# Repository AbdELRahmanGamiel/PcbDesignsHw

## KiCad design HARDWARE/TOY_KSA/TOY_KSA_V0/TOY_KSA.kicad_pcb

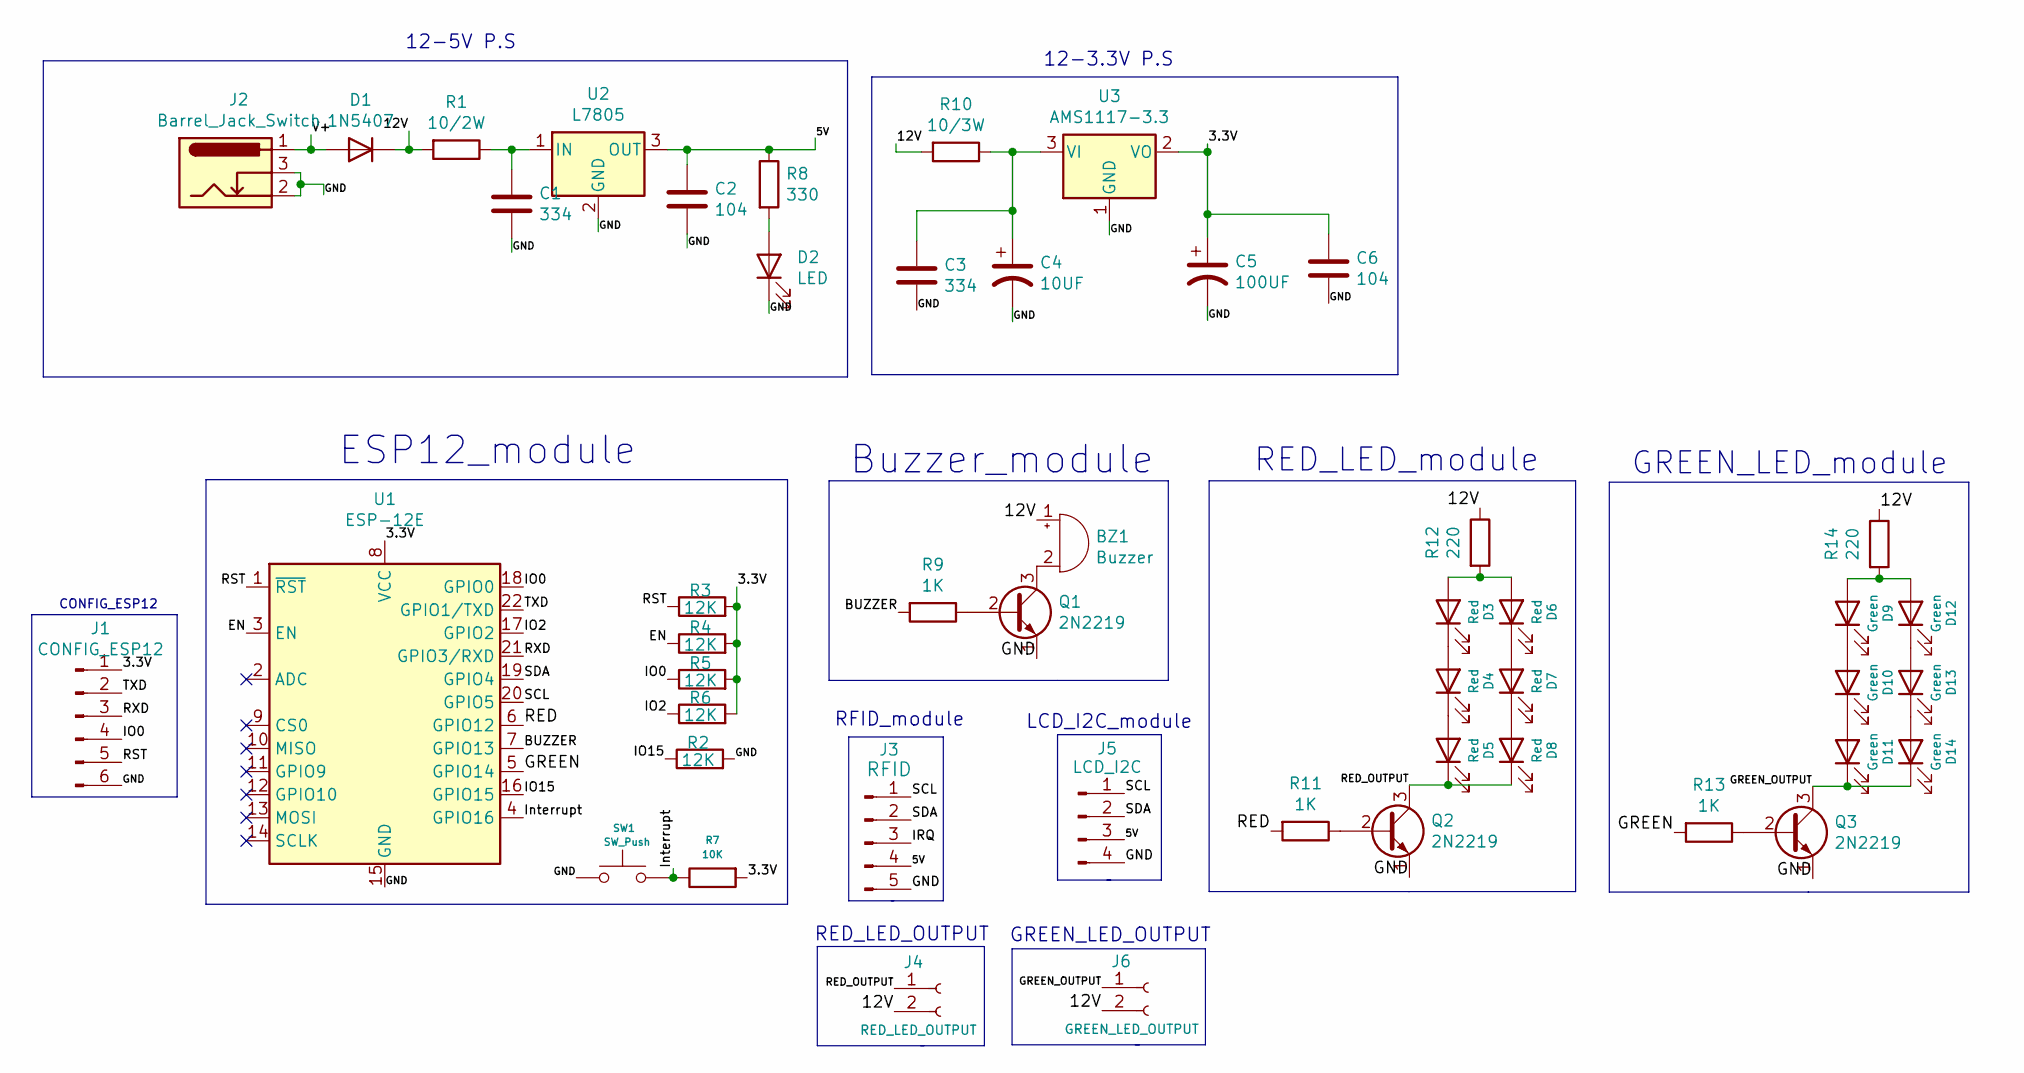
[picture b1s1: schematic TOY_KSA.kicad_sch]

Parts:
BZ1: Buzzer; Buzzer_12x9.5RM7.6
C1, C3: 334; C_0805_2012Metric_Pad1.18x1.45mm_HandSolder
C2, C6: 104; C_0805_2012Metric_Pad1.18x1.45mm_HandSolder
C4: 10UF; CP_Radial_D5.0mm_P2.00mm
C5: 100UF; CP_Radial_D8.0mm_P3.50mm
D1: 1N5407; D_SMA_Handsoldering
D2: LED; LED_0805_2012Metric_Pad1.15x1.40mm_HandSolder
D3, D4, D5, D6, D7, D8: Red; LED_0805_2012Metric_Pad1.15x1.40mm_HandSolder
D9, D10, D11, D12, D13, D14: Green; LED_0805_2012Metric_Pad1.15x1.40mm_HandSolder
J1: CONFIG_ESP12; PinHeader_1x06_P2.54mm_Vertical
J2: Barrel_Jack_Switch; BarrelJack_Horizontal
J3: RFID; PinHeader_1x05_P2.54mm_Vertical
J4: RED_LED_OUTPUT; PinHeader_1x02_P2.54mm_Vertical
J5: LCD_I2C; PinHeader_1x04_P2.54mm_Vertical
J6: GREEN_LED_OUTPUT; PinHeader_1x02_P2.54mm_Vertical
Q1, Q2, Q3: 2N2219; TO-92L_Wide
R1: 10/2W; R_Axial_Power_L20.0mm_W6.4mm_P25.40mm
R2, R3, R4, R5, R6: 12K; R_0805_2012Metric_Pad1.20x1.40mm_HandSolder
R7: 10K; R_0805_2012Metric_Pad1.20x1.40mm_HandSolder
R8: 330; R_0805_2012Metric_Pad1.20x1.40mm_HandSolder
R9, R11, R13: 1K; R_0805_2012Metric_Pad1.20x1.40mm_HandSolder
R10: 10/3W; R_Axial_Power_L20.0mm_W6.4mm_P25.40mm
R12, R14: 220; R_0805_2012Metric_Pad1.20x1.40mm_HandSolder
SW1: SW_Push; SW_PUSH_6mm_H7.3mm
U1: ESP-12E
U2: L7805; SOT-223-3_TabPin2
U3: AMS1117-3.3; SOT-223-3_TabPin2

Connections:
/3.3V: C5.1, C6.1, J1.1, R3.2, R4.2, R5.2, R6.2, R7.2, U1.8 (VCC), U3.2 (VO)
/5V: C2.1, J3.4, J5.3, R8.1, U2.3 (OUT)
/12V: BZ1.1 (-), D1.1 (K), J4.2, J6.2, R1.2, R10.2, R12.1, R14.1
/BUZZER: R9.2, U1.7 (GPIO13)
/EN: R4.1, U1.3 (EN)
/GND: C1.2, C2.2, C3.2, C4.2, C5.2, C6.2, D2.1 (K), J1.6, J2.2, J2.3, J3.5, J5.4, Q1.1 (E), Q2.1 (E), Q3.1 (E), R2.2, SW1.1, U1.15 (GND), U2.2 (GND), U3.1 (GND)
/GREEN: R13.2, U1.5 (GPIO14)
/GREEN_OUTPUT: D11.1 (K), D14.1 (K), J6.1, Q3.3 (C)
/IO0: J1.4, R5.1, U1.18 (GPIO0)
/IO2: R6.1, U1.17 (GPIO2)
/IO15: R2.1, U1.16 (GPIO15)
/IRQ: J3.3
/Interrupt: R7.1, SW1.2, U1.4 (GPIO16)
/RED: R11.2, U1.6 (GPIO12)
/RED_OUTPUT: D5.1 (K), D8.1 (K), J4.1, Q2.3 (C)
/RST: J1.5, R3.1, U1.1 (~RST)
/RXD: J1.3, U1.21 (GPIO3/RXD)
/SCL: J3.1, J5.1, U1.20 (GPIO5)
/SDA: J3.2, J5.2, U1.19 (GPIO4)
/TXD: J1.2, U1.22 (GPIO1/TXD)
/V+: D1.2 (A), J2.1
unnamed: BZ1.2 (+), Q1.3 (C)
unnamed: C1.1, R1.1, U2.1 (IN)
unnamed: C3.1, C4.1, R10.1, U3.3 (VI)
unnamed: D2.2 (A), R8.2
unnamed: D3.1 (K), D4.2 (A)
unnamed: D3.2 (A), D6.2 (A), R12.2
unnamed: D4.1 (K), D5.2 (A)
unnamed: D6.1 (K), D7.2 (A)
unnamed: D7.1 (K), D8.2 (A)
unnamed: D10.1 (K), D11.2 (A)
unnamed: D9.1 (K), D10.2 (A)
unnamed: D12.1 (K), D13.2 (A)
unnamed: D9.2 (A), D12.2 (A), R14.2
unnamed: D13.1 (K), D14.2 (A)
unnamed: Q1.2 (B), R9.1
unnamed: Q2.2 (B), R11.1
unnamed: Q3.2 (B), R13.1

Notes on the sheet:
GREEN_LED_module
ESP12_module
GREEN_LED_OUTPUT
RED_LED_module
Buzzer_module
12-3.3V P.S
CONFIG_ESP12
12-5V P.S
RFID_module
LCD_I2C_module
RED_LED_OUTPUT

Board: 2 copper layers, 48 parts (0 on the bottom side), 37 nets, no tracks yet.

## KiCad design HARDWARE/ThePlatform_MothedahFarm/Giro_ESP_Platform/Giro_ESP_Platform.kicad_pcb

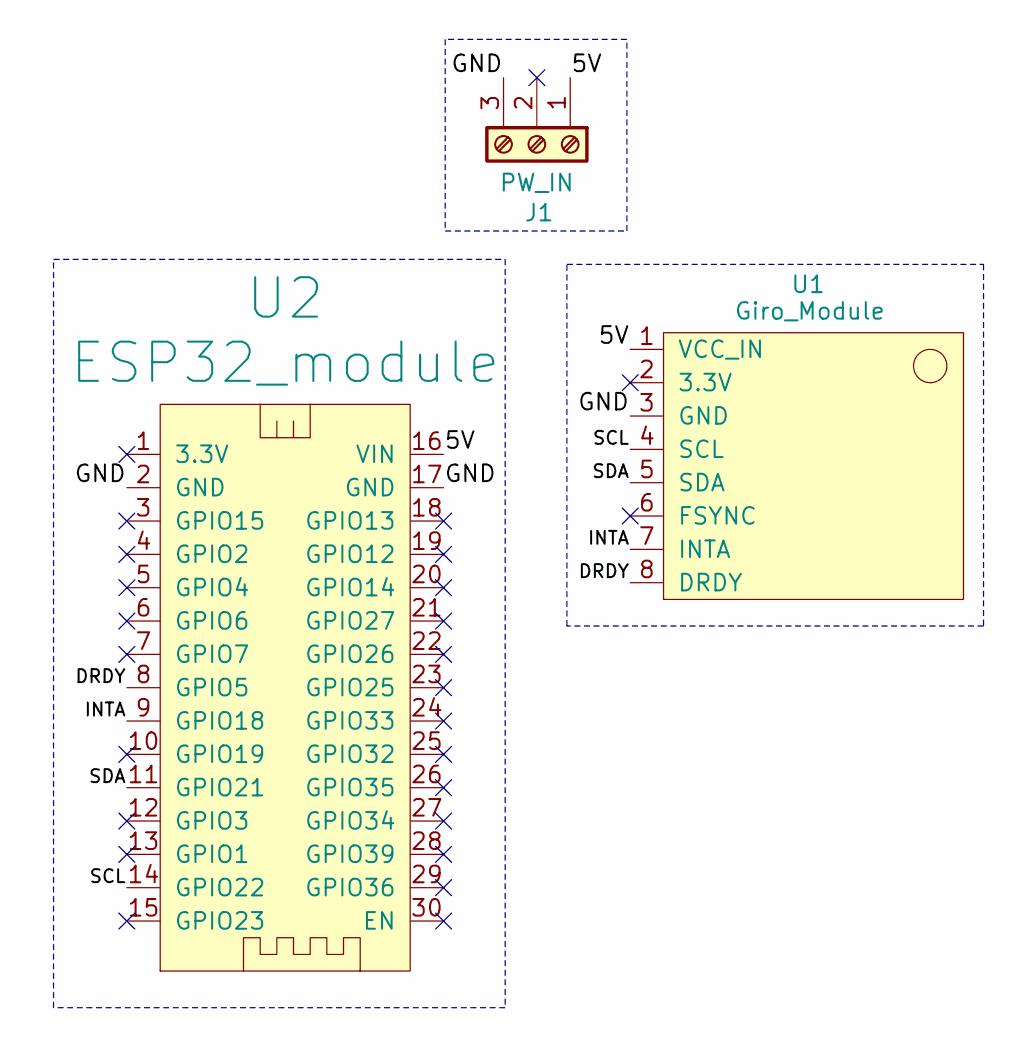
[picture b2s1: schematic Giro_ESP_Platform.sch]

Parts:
J1: PW_IN; PhoenixContact_MSTBA_2,5_3-G-5,08_1x03_P5.08mm_Horizontal
U1: Giro_Module
U2: ESP32_module

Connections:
/5V: J1.1, U1.1 (VCC_IN), U2.16 (VIN)
/DRDY: U1.8 (DRDY), U2.8 (GPIO5)
/GND: J1.3, U1.3 (GND), U2.2 (GND), U2.17 (GND)
/INTA: U1.7 (INTA), U2.9 (GPIO18)
/SCL: U1.4 (SCL), U2.14 (GPIO22)
/SDA: U1.5 (SDA), U2.11 (GPIO21)

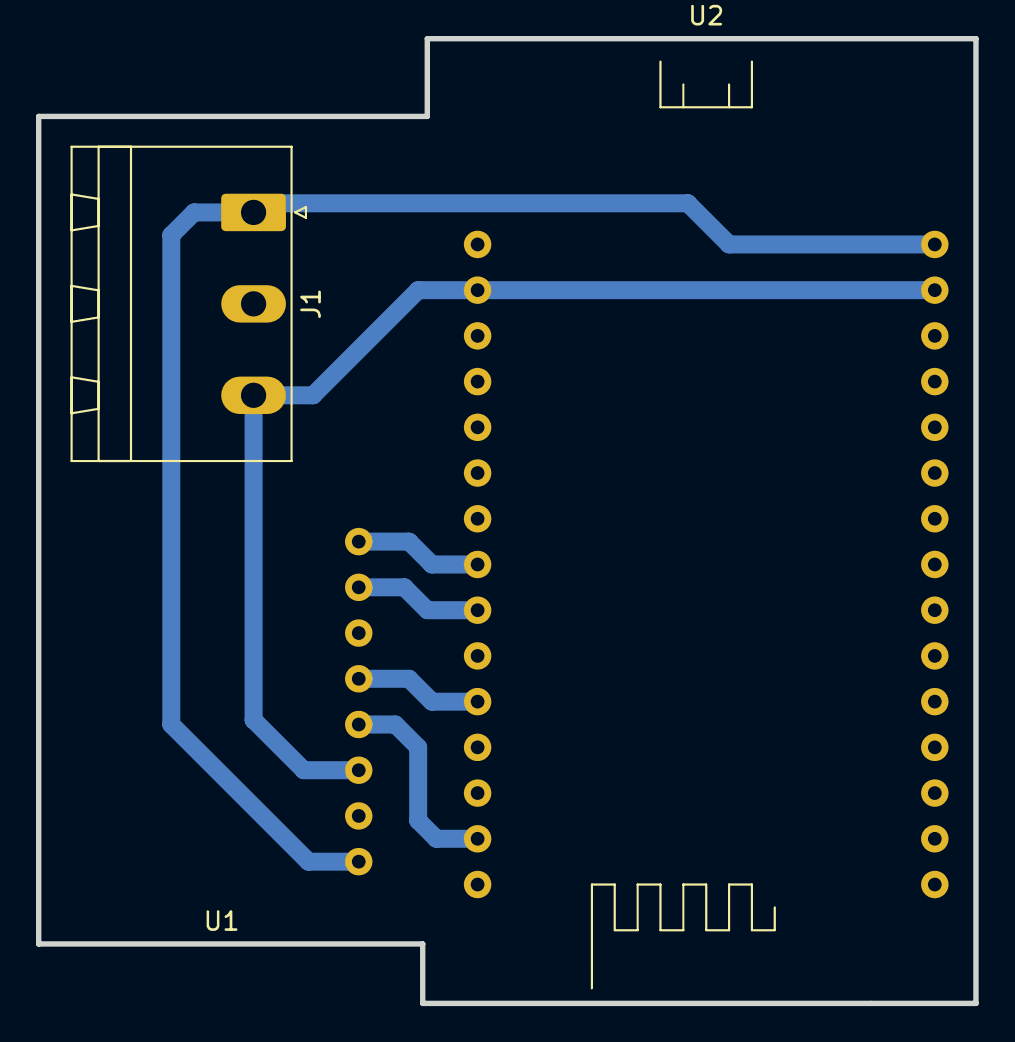
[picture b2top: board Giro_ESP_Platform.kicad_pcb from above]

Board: 2 copper layers, 52.1 x 53.6 mm, 3 parts (0 on the bottom side), 6 nets.

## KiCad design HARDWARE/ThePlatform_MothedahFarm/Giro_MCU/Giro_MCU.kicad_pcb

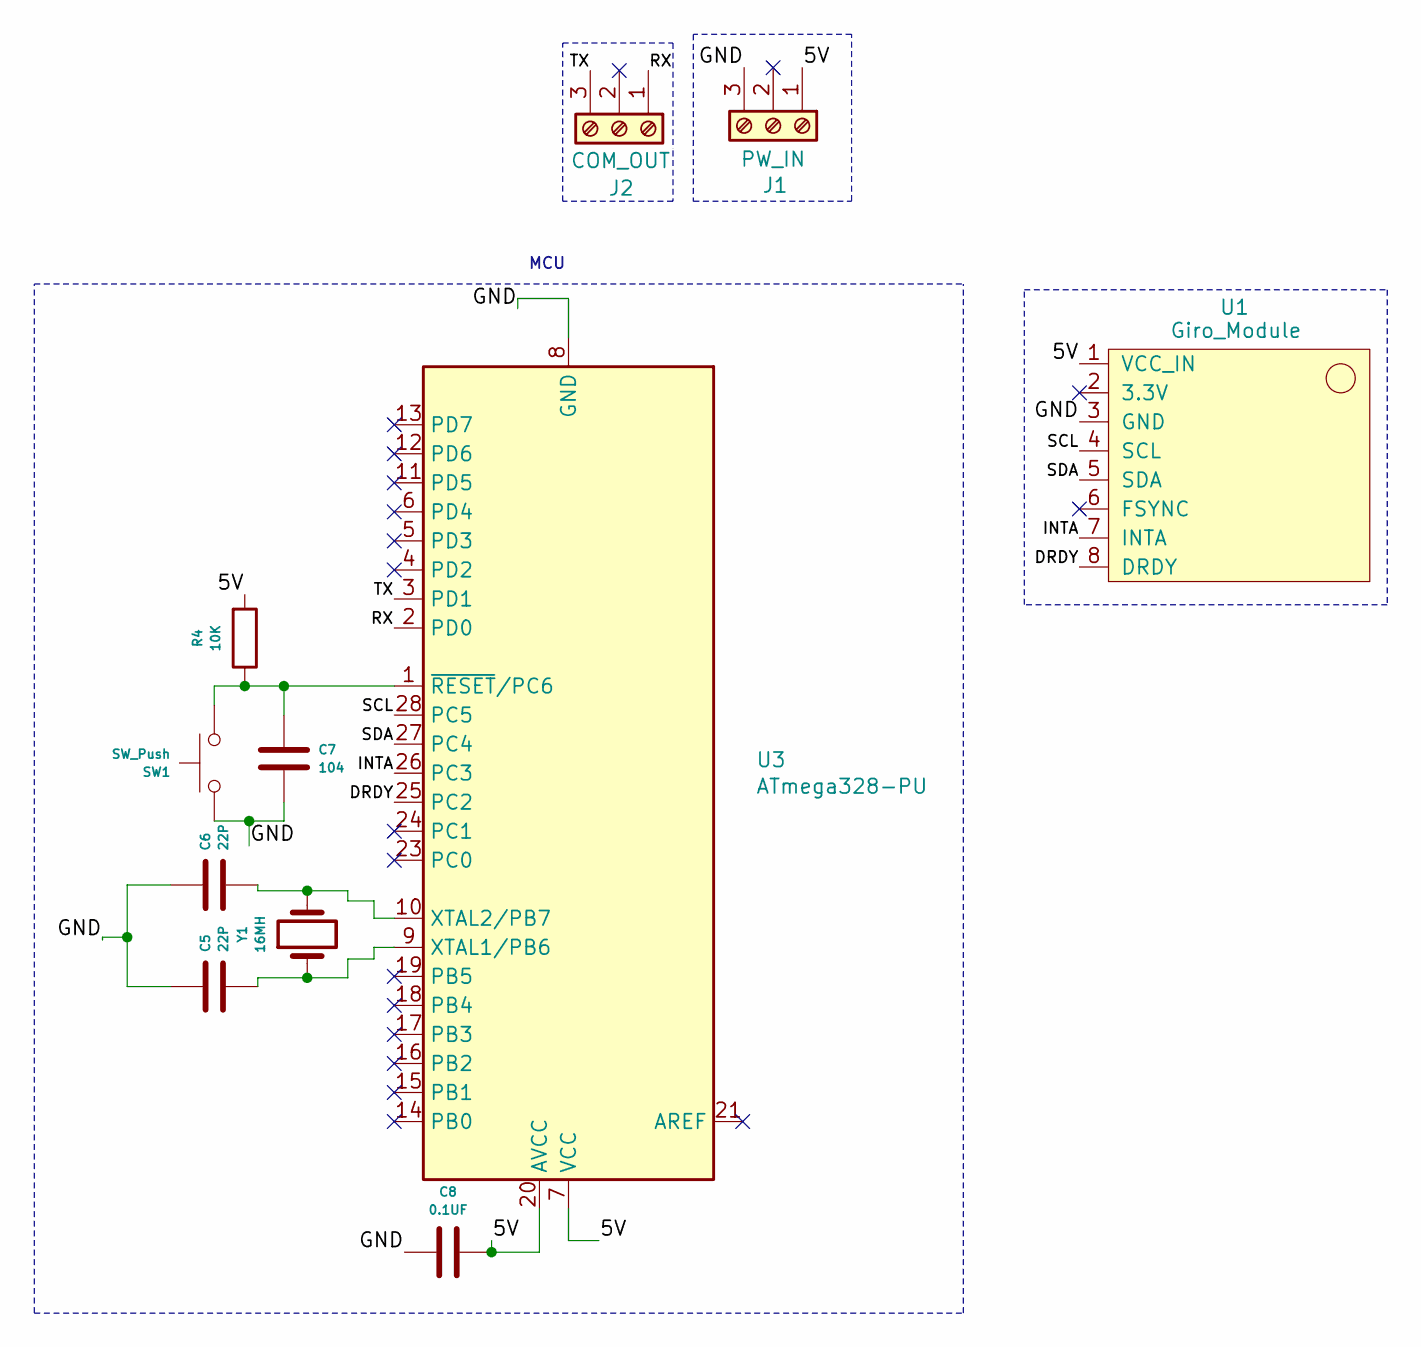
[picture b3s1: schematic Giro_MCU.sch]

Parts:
C5, C6: 22P; C_Disc_D7.0mm_W2.5mm_P5.00mm
C7: 104; C_Disc_D7.0mm_W2.5mm_P5.00mm
C8: 0.1UF; C_Disc_D7.0mm_W2.5mm_P5.00mm
J1: PW_IN; PhoenixContact_MSTBA_2,5_3-G-5,08_1x03_P5.08mm_Horizontal
J2: COM_OUT; PhoenixContact_MSTBA_2,5_3-G-5,08_1x03_P5.08mm_Horizontal
R4: 10K; R_Axial_DIN0207_L6.3mm_D2.5mm_P10.16mm_Horizontal
SW1: SW_Push; SW_PUSH_6mm_H7.3mm
U1: Giro_Module
U3: ATmega328-PU; DIP-28_W7.62mm_Socket_LongPads
Y1: 16MH; Resonator-2Pin_W10.0mm_H5.0mm

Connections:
/5V: C8.1, J1.1, R4.2, U1.1 (VCC_IN), U3.7 (VCC), U3.20 (AVCC)
/DRDY: U1.8 (DRDY), U3.25 (PC2)
/GND: C5.2, C6.2, C7.1, C8.2, J1.3, SW1.1, U1.3 (GND), U3.8 (GND), U3.22 (GND)
/INTA: U1.7 (INTA), U3.26 (PC3)
/RX: J2.1, U3.2 (PD0)
/SCL: U1.4 (SCL), U3.28 (PC5)
/SDA: U1.5 (SDA), U3.27 (PC4)
/TX: J2.3, U3.3 (PD1)
unnamed: C5.1, U3.9 (XTAL1/PB6), Y1.1
unnamed: C6.1, U3.10 (XTAL2/PB7), Y1.2
unnamed: C7.2, R4.1, SW1.2, U3.1 (~RESET~/PC6)

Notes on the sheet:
MCU

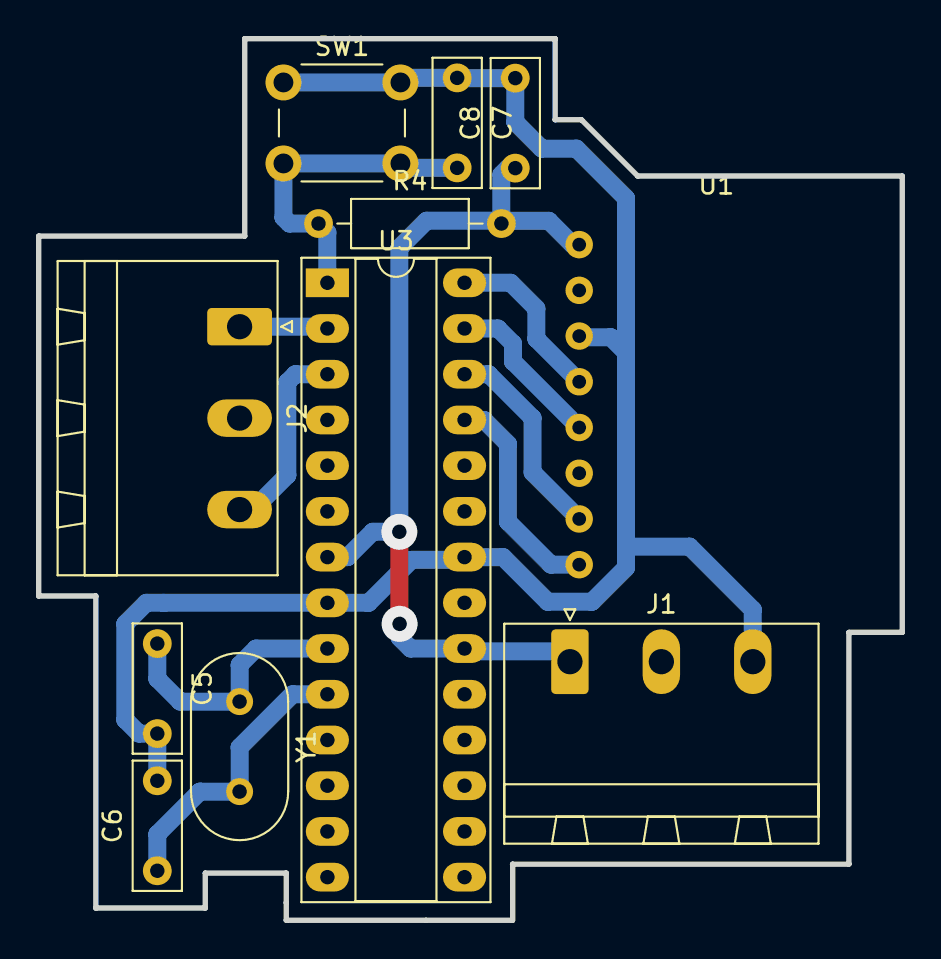
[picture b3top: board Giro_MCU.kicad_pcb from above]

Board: 2 copper layers, 48.0 x 49.0 mm, 11 parts (0 on the bottom side), 11 nets.

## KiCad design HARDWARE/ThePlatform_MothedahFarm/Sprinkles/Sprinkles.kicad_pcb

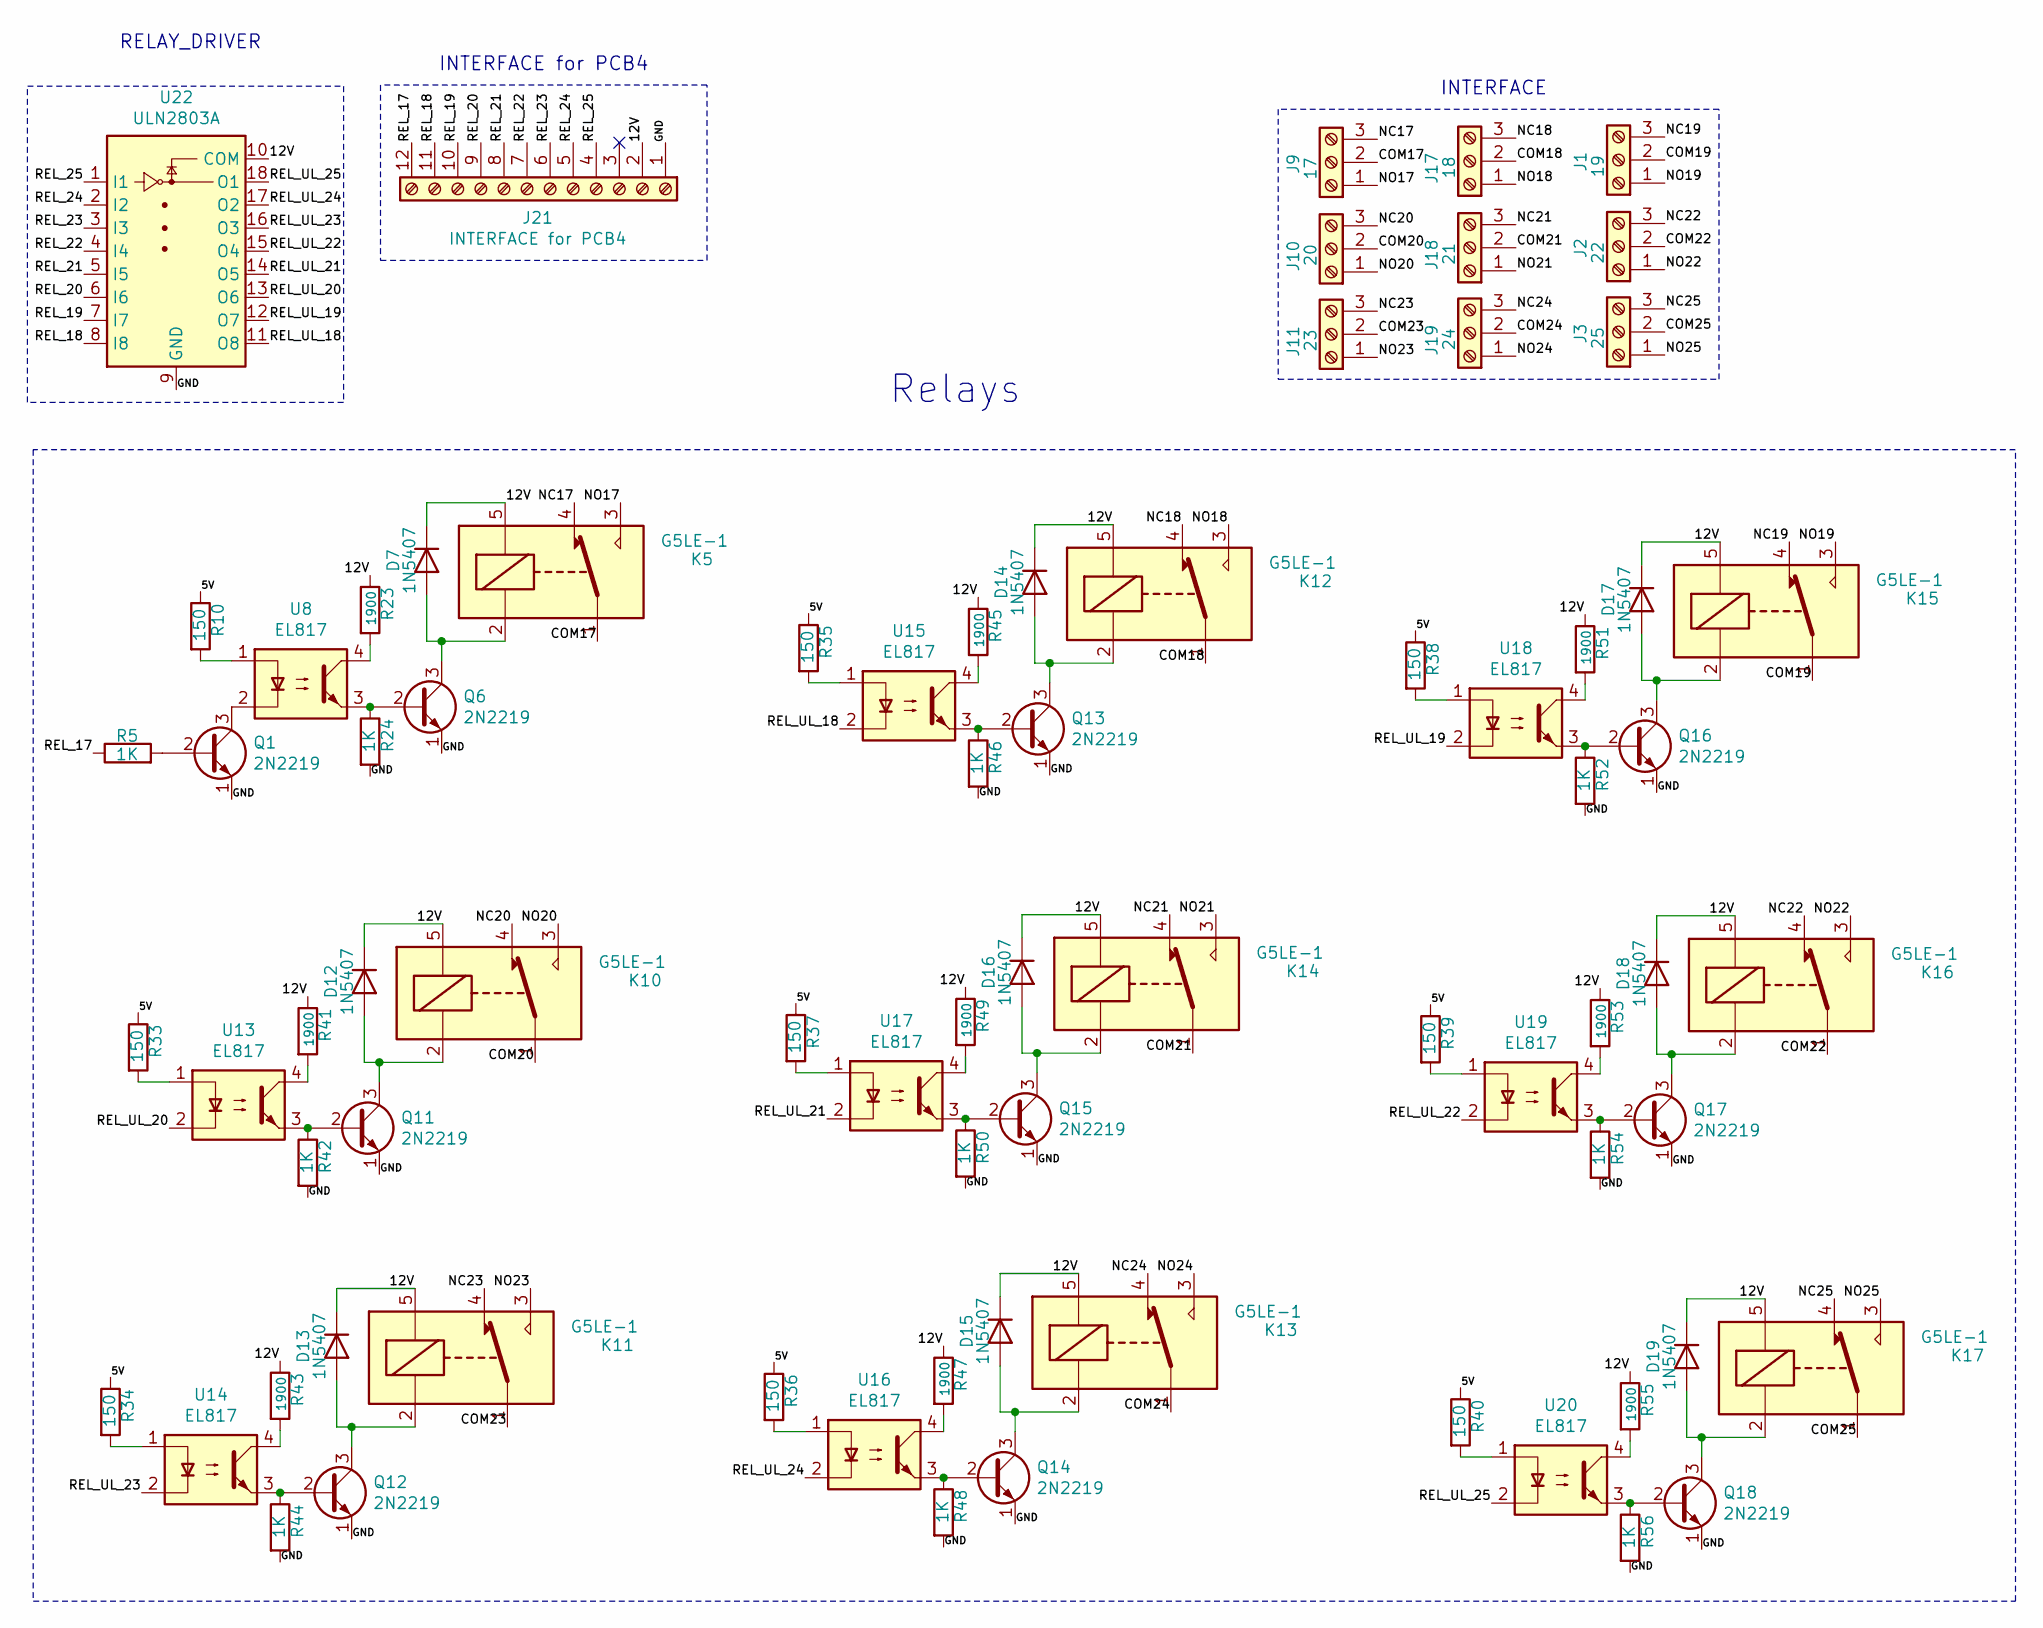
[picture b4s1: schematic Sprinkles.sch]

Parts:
D7, D12, D13, D14, D15, D16, D17, D18, D19: 1N5407; D_DO-15_P12.70mm_Horizontal
J1: 19; PhoenixContact_MSTBA_2,5_3-G-5,08_1x03_P5.08mm_Horizontal
J2: 22; PhoenixContact_MSTBA_2,5_3-G-5,08_1x03_P5.08mm_Horizontal
J3: 25; PhoenixContact_MSTBA_2,5_3-G-5,08_1x03_P5.08mm_Horizontal
J9: 17; PhoenixContact_MSTBA_2,5_3-G-5,08_1x03_P5.08mm_Horizontal
J10: 20; PhoenixContact_MSTBA_2,5_3-G-5,08_1x03_P5.08mm_Horizontal
J11: 23; PhoenixContact_MSTBA_2,5_3-G-5,08_1x03_P5.08mm_Horizontal
J17: 18; PhoenixContact_MSTBA_2,5_3-G-5,08_1x03_P5.08mm_Horizontal
J18: 21; PhoenixContact_MSTBA_2,5_3-G-5,08_1x03_P5.08mm_Horizontal
J19: 24; PhoenixContact_MSTBA_2,5_3-G-5,08_1x03_P5.08mm_Horizontal
J21: INTERFACE for PCB4; PhoenixContact_MSTBA_2,5_12-G-5,08_1x12_P5.08mm_Horizontal
K5, K10, K11, K12, K13, K14, K15, K16, K17: G5LE-1; Relay_SPDT_Omron-G5LE-1
Q1, Q6, Q11, Q12, Q13, Q14, Q15, Q16, Q17, Q18: 2N2219; TO-92L_Wide
R5, R24, R42, R44, R46, R48, R50, R52, R54, R56: 1K; R_Axial_DIN0207_L6.3mm_D2.5mm_P10.16mm_Horizontal
R10, R33, R34, R35, R36, R37, R38, R39, R40: 150; R_Axial_DIN0207_L6.3mm_D2.5mm_P10.16mm_Horizontal
R23, R41, R43, R45, R47, R49, R51, R53, R55: 1900; R_Axial_DIN0207_L6.3mm_D2.5mm_P10.16mm_Horizontal
U8, U13, U14, U15, U16, U17, U18, U19, U20: EL817; DIP-4_W7.62mm
U22: ULN2803A; DIP-18_W7.62mm_Socket_LongPads

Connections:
/5V: R10.1, R33.1, R34.1, R35.1, R36.1, R37.1, R38.1, R39.1, R40.1
/12V: D7.1 (K), D12.1 (K), D13.1 (K), D14.1 (K), D15.1 (K), D16.1 (K), D17.1 (K), D18.1 (K), D19.1 (K), J21.2, K5.5, K10.5, K11.5, K12.5, K13.5, K14.5, K15.5, K16.5, K17.5, R23.1, R41.1, R43.1, R45.1, R47.1, R49.1, R51.1, R53.1, R55.1, U22.10 (COM)
/COM17: J9.2, K5.1
/COM18: J17.2, K12.1
/COM19: J1.2, K15.1
/COM20: J10.2, K10.1
/COM21: J18.2, K14.1
/COM22: J2.2, K16.1
/COM23: J11.2, K11.1
/COM24: J19.2, K13.1
/COM25: J3.2, K17.1
/GND: J21.1, Q1.1 (E), Q6.1 (E), Q11.1 (E), Q12.1 (E), Q13.1 (E), Q14.1 (E), Q15.1 (E), Q16.1 (E), Q17.1 (E), Q18.1 (E), R24.2, R42.2, R44.2, R46.2, R48.2, R50.2, R52.2, R54.2, R56.2, U22.9 (GND)
/NC17: J9.3, K5.4
/NC18: J17.3, K12.4
/NC19: J1.3, K15.4
/NC20: J10.3, K10.4
/NC21: J18.3, K14.4
/NC22: J2.3, K16.4
/NC23: J11.3, K11.4
/NC24: J19.3, K13.4
/NC25: J3.3, K17.4
/NO17: J9.1, K5.3
/NO18: J17.1, K12.3
/NO19: J1.1, K15.3
/NO20: J10.1, K10.3
/NO21: J18.1, K14.3
/NO22: J2.1, K16.3
/NO23: J11.1, K11.3
/NO24: J19.1, K13.3
/NO25: J3.1, K17.3
/REL_17: J21.12, R5.1
/REL_18: J21.11, U22.8 (I8)
/REL_19: J21.10, U22.7 (I7)
/REL_20: J21.9, U22.6 (I6)
/REL_21: J21.8, U22.5 (I5)
/REL_22: J21.7, U22.4 (I4)
/REL_23: J21.6, U22.3 (I3)
/REL_24: J21.5, U22.2 (I2)
/REL_25: J21.4, U22.1 (I1)
/REL_UL_18: U15.2, U22.11 (O8)
/REL_UL_19: U18.2, U22.12 (O7)
/REL_UL_20: U13.2, U22.13 (O6)
/REL_UL_21: U17.2, U22.14 (O5)
/REL_UL_22: U19.2, U22.15 (O4)
/REL_UL_23: U14.2, U22.16 (O3)
/REL_UL_24: U16.2, U22.17 (O2)
/REL_UL_25: U20.2, U22.18 (O1)
unnamed: D7.2 (A), K5.2, Q6.3 (C)
unnamed: D12.2 (A), K10.2, Q11.3 (C)
unnamed: D13.2 (A), K11.2, Q12.3 (C)
unnamed: D14.2 (A), K12.2, Q13.3 (C)
unnamed: D15.2 (A), K13.2, Q14.3 (C)
unnamed: D16.2 (A), K14.2, Q15.3 (C)
unnamed: D17.2 (A), K15.2, Q16.3 (C)
unnamed: D18.2 (A), K16.2, Q17.3 (C)
unnamed: D19.2 (A), K17.2, Q18.3 (C)
unnamed: Q1.2 (B), R5.2
unnamed: Q1.3 (C), U8.2
unnamed: Q6.2 (B), R24.1, U8.3
unnamed: Q11.2 (B), R42.1, U13.3
unnamed: Q12.2 (B), R44.1, U14.3
unnamed: Q13.2 (B), R46.1, U15.3
unnamed: Q14.2 (B), R48.1, U16.3
unnamed: Q15.2 (B), R50.1, U17.3
unnamed: Q16.2 (B), R52.1, U18.3
unnamed: Q17.2 (B), R54.1, U19.3
unnamed: Q18.2 (B), R56.1, U20.3
unnamed: R10.2, U8.1
unnamed: R23.2, U8.4
unnamed: R33.2, U13.1
unnamed: R34.2, U14.1
unnamed: R35.2, U15.1
unnamed: R36.2, U16.1
unnamed: R37.2, U17.1
unnamed: R38.2, U18.1
unnamed: R39.2, U19.1
unnamed: R40.2, U20.1
unnamed: R41.2, U13.4
unnamed: R43.2, U14.4
unnamed: R45.2, U15.4
unnamed: R47.2, U16.4
unnamed: R49.2, U17.4
unnamed: R51.2, U18.4
unnamed: R53.2, U19.4
unnamed: R55.2, U20.4

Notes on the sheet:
Relays
INTERFACE for PCB4
RELAY_DRIVER
INTERFACE

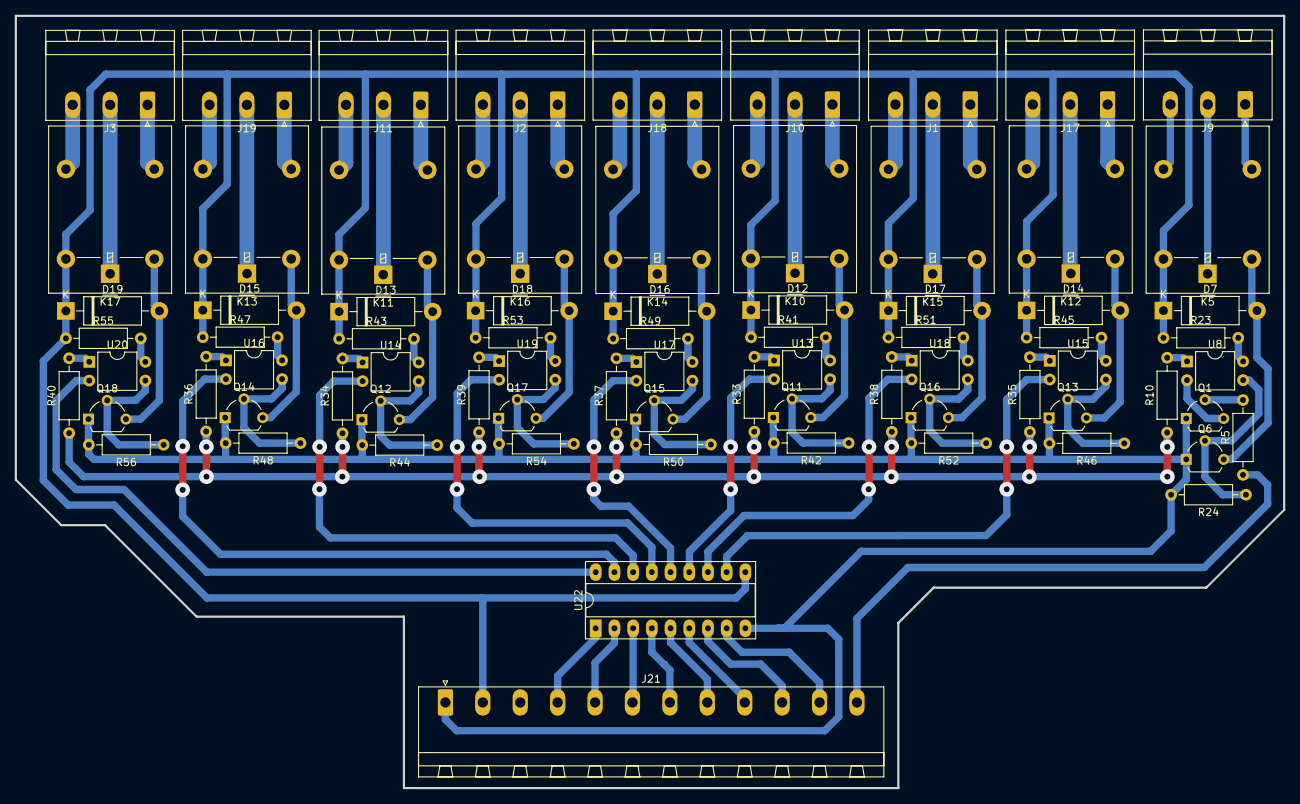
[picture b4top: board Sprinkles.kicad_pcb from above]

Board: 2 copper layers, 172.2 x 104.9 mm, 76 parts (0 on the bottom side), 85 nets.
